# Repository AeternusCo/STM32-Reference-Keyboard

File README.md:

# STM32 Keyboard Reference Project

## WARNING

This schematic has not been officially tested. It follows best practices and should work, but please confirm your design before placing a large order!

PCBs have been ordered to confirm the design works as intended, this warning will be removed once the design is verified.

## Goals

The primary goal of this project is to provide a semi-opinionated starting point for people new to STM32 microcontrollers.
A majority of commonly used keyboard features are broken out on pins that are best suited for the purpose. (RGB on SPI, split on USART, etc)

A secondary goal of this project is to provide a schematic that allows for swapping between a number of readily available STM32 MCUs based on need and availability.

An example BOM is listed below, while a majority of parts are JLCPCB basic parts, the goal of this project is not to provide a _cheap_ project, but a common project.

Components used are 0603 or larger as to make hand solderability as easy as possible for the designer.

## Libraries Used

The following non-standard libraries were used to design this project:

- [ai03-2725/Type-C.pretty](https://github.com/ai03-2725/Type-C.pretty)
- [ai03-2725/MX_Alps_Hybrid/MXOnly.pretty](https://github.com/ai03-2725/MX_Alps_Hybrid)

It is recommended to include these as global libraries in KiCAD, as they are very commonly used on most keyboard projects.

## Pictures

### Schematic

### PCB

## BOM

| Designator | Description | Package | LCSC Part Number |
|-----------|-----------| -------|-----------------|
|Y1|8MHz|SMD-5032_2P|C115962|
|USB1|HRO-TYPE-C-31-M-12|HRO-TYPE-C-31-M-12|C165948|
|U1|STM32F072CBTx|LQFP-48_7x7mm_P0.5mm|C81720|
|U2|SRV05-4|SOT-23-6|C85364|
|U3|MCP1700T-3302E_SOT23|SOT-23|C39051|
|RESET1|SW_Push|SMD-SW-4_5.1x5.1x1.5|C318884|
|R_SHIELD1|1M|0603|C22935|
|R_RGB1,R_BOOT1|10k|0603|C25804|
|R_LDO2,R_LDO1|100k|0603|C25803|
|R_I2C2,R_I2C1|4.7k|0603|C23162|
|R_CC2,R_CC1|5.1k|0603|C23186|
|R_USB1|1.5k|0603|C328342|
|F1|500mA|1206|C151162|
|D_PWR1|SMF9.0CA|SOD-123|C123799|
|D_LDO1|RB060MM-60TR|SOD-123|C115330|
|D4,D3,D2,D1|CD4148W|0603|C109002|
|C_XTAL2,C_XTAL1|30pF|0603|C22397|
|C_VDDIO2,C_VDD2,C_VDD1|100n|0603|C14663|
|C_VDDIO1,C_VDD3|4.7u|0603|C19666|
|C_VDDA2,C_LDO2,C_LDO1|1u|0603|C15849|
|C_VDDA1|10u|0603|C19702|
|C_SHIELD1|4.7n|0603|C53987|
|BOOT1|SW_SPDT|SW_SPDT_PCM12|C221841|

## License

This project is licensed under the Unlicense. Please see [LICENSE](LICENSE) for more information.

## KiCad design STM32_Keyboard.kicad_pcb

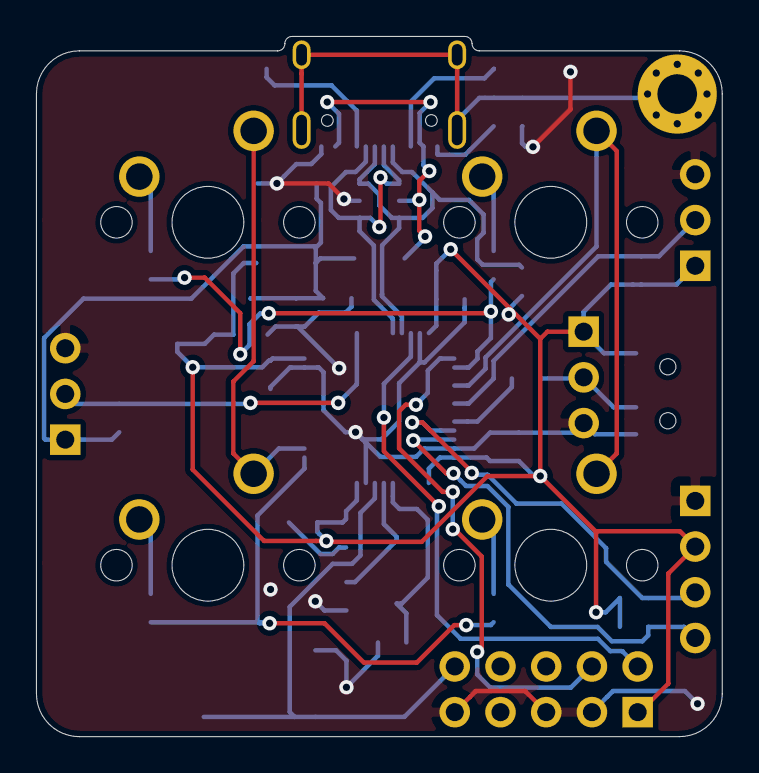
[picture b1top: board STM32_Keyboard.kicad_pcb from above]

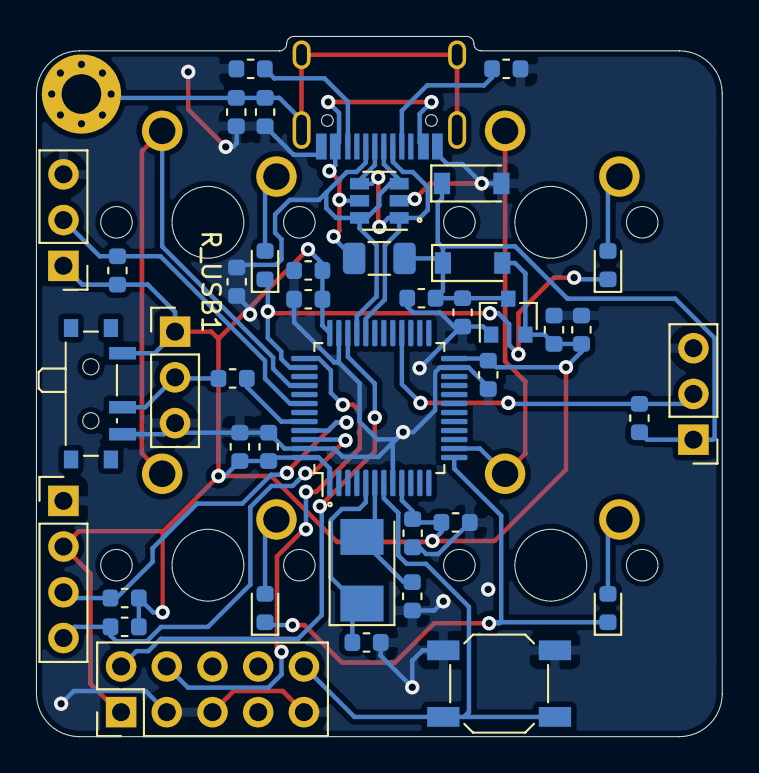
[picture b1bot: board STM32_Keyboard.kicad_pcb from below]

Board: 2 copper layers, 38.1 x 38.9 mm, 47 parts (43 on the bottom side), 28 nets.

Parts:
BOOT1: SW_SPDT; SW_SPDT_PCM12
CHASSIS1: Chassis; MountingHole_2.2mm_M2_Pad_Via
C_LDO1, C_LDO2: 1u; C_0603_1608Metric
C_SHIELD1: 4.7n; C_0603_1608Metric
C_VDD1, C_VDD2: 100n; C_0603_1608Metric
C_VDD3: 4.7u; C_0603_1608Metric
C_VDDA1: 10u; C_0603_1608Metric
C_VDDA2: 1u; C_0603_1608Metric
C_VDDIO1: 4.7u; C_0603_1608Metric
C_VDDIO2: 100n; C_0603_1608Metric
C_XTAL1, C_XTAL2: 30pF; C_0603_1608Metric
D1, D2, D3, D4: CD4148W; D_0603_1608Metric
D_LDO1: RB060MM-60TR; D_SOD-123
D_PWR1: SMF9.0CA; D_SOD-123
F1: 500mA; Fuse_1206_3216Metric
J_BOOT1: Conn_01x03; PinHeader_1x03_P2.54mm_Vertical
J_I2C1: Conn_01x04; PinHeader_1x04_P2.54mm_Vertical
J_RGB1: Conn_01x03; PinHeader_1x03_P2.54mm_Vertical
J_SPLIT1: Conn_01x03; PinHeader_1x03_P2.54mm_Vertical
J_SWD1: SWD; PinHeader_2x05_P2.54mm_Vertical
RESET1: SW_Push; SW_SPST_SKQG_WithStem
R_BOOT1: 10k; R_0603_1608Metric
R_CC1, R_CC2: 5.1k; R_0603_1608Metric
R_I2C1, R_I2C2: 4.7k; R_0603_1608Metric
R_LDO1, R_LDO2: 100k; R_0603_1608Metric
R_RGB1: 10k; R_0603_1608Metric
R_SHIELD1: 1M; R_0603_1608Metric
R_SPLIT1: 4.7k; R_0603_1608Metric
R_USB1: 1.5k; R_0603_1608Metric
SW1, SW2, SW3, SW4: SW_Push; MXOnly-1U-NoLED
U1: STM32F072CBTx; LQFP-48_7x7mm_P0.5mm
U2: SRV05-4; SOT-23-6
U3: MCP1700T-3302E_SOT23; SOT-23
USB1: HRO-TYPE-C-31-M-12
Y1: 8MHz; Crystal_SMD_5032-2Pin_5.0x3.2mm

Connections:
+3V3: BOOT1.1, C_LDO2.1, C_VDD1.1, C_VDD2.1, C_VDD3.1, C_VDDA1.1, C_VDDA2.1, C_VDDIO1.1, C_VDDIO2.1, D_LDO1.2, J_BOOT1.1, J_I2C1.2, J_SPLIT1.1, J_SWD1.1, R_I2C1.1, R_I2C2.1, R_LDO2.1, R_SPLIT1.1, R_USB1.1, U1.1, U1.9, U1.24, U1.36, U1.48, U3.2
+5V: C_LDO1.1, D_LDO1.1, D_PWR1.1, F1.1, J_RGB1.1, R_LDO1.1, R_RGB1.1, U3.3
A3: D3.1, D4.1, U1.13
A4: SW1.2, SW3.2, U1.14
A13: J_SWD1.2, U1.34
A14: J_SWD1.4, U1.37
A15: D1.1, D2.1, U1.38
B4: SW2.2, SW4.2, U1.40
B6: J_SPLIT1.2, R_SPLIT1.2, U1.42
B8: J_I2C1.3, R_I2C1.2, U1.45
B9: J_I2C1.4, R_I2C2.2, U1.46
B15: J_RGB1.2, R_RGB1.2, U1.28
BOOT0: R_BOOT1.2, U1.44
Earth: CHASSIS1.1, C_SHIELD1.2, R_SHIELD1.2, USB1.13
GND: BOOT1.3, C_LDO1.2, C_LDO2.2, C_SHIELD1.1, C_VDD1.2, C_VDD2.2, C_VDD3.2, C_VDDA1.2, C_VDDA2.2, C_VDDIO1.2, C_VDDIO2.2, C_XTAL1.2, C_XTAL2.2, D_PWR1.2, J_BOOT1.3, J_I2C1.1, J_RGB1.3, J_SPLIT1.3, J_SWD1.3, J_SWD1.5, J_SWD1.9, RESET1.2, R_CC1.1, R_CC2.1, R_LDO1.2, R_LDO2.2, R_SHIELD1.1, U1.8, U1.23, U1.35, U1.47, U2.2, U3.1, USB1.1, USB1.12
NRST: J_SWD1.10, RESET1.1, U1.7
unnamed: BOOT1.2, J_BOOT1.2, R_BOOT1.1
unnamed: D1.2, SW1.1
unnamed: D2.2, SW2.1
unnamed: D3.2, SW3.1
unnamed: D4.2, SW4.1
unnamed: R_CC1.2, USB1.4
unnamed: R_CC2.2, USB1.10
USB_D+: R_USB1.2, U1.33, U2.3, U2.6, USB1.6, USB1.8
USB_D-: U1.32, U2.1, U2.4, USB1.5, USB1.7
VCC: F1.2, U2.5, USB1.2, USB1.11
XTAL_IN: C_XTAL1.1, U1.5, Y1.1
XTAL_OUT: C_XTAL2.1, U1.6, Y1.2

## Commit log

2020-10-23 Initial commit.
2020-10-23 Updated ai03-2725 library references in README to point to respective repositories.
2020-10-23 Added schematic screenshot.
2020-10-23 Formatted BOM.
2020-10-23 Added reference BOM.
2020-10-23 Fixed formatting issues in BOM.
2020-10-23 Reorganized BOM.
2020-10-23 Added warning to README.
2020-10-23 Removed 3d model reference.
2020-10-27 Added 1.5kΩ USB D+ pull up resistor.
